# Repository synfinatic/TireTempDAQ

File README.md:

# TireTempDAQ

## About
This project is designed to add IR  temperature sensors to your existing data logger.  The initial design for this project will support up to 4 sensors and output 4 linear analog outputs (0 to 4.096V) to your data logger (GPX Pro, AiM, Race-Technology, AEM, MoTeC, GEMS, etc).

This project will include three main parts:

 * CadSoft Eagle files for the PCB designs
 * Arduino compatible software for the [PRJC Teensy-LC](http://www.prjc.com/teensy/teensyLC.html) micro-controller
 * [Autodesk Fusion 360](http://www.autodesk.com/products/fusion-360/overview) CAD designs of the cases for the sensor & controller modules which can then be manufactured via 3D printing ABS/PLA or CNC aluminum.
 
## Design
The key component will be the [Melexis MXL90614](http://www.melexis.com/Infrared-Thermometer-Sensors/Infrared-Thermometer-Sensors/Digital-plug--play-infrared-thermometer-in-a-TO-can-615.aspx) IR temperature sensor.  This sensor is a small yet accurate IR sensor able to measure the temperature of other objects without touching them- perfect for tires on a car or motorcycle!

Each sensor sends it's data via a thin single cable of 4 wires to the "brains" which decodes the digital signals from each sensor and then relays that to your data logger via a standard linear analog output.  This conversion process ensures that TireTempDAQ will be compatible with virtually any data aquision system you can imagine!

## License
All files are released under the [GPLv3](http://www.gnu.org/licenses/gpl-3.0.en.html).

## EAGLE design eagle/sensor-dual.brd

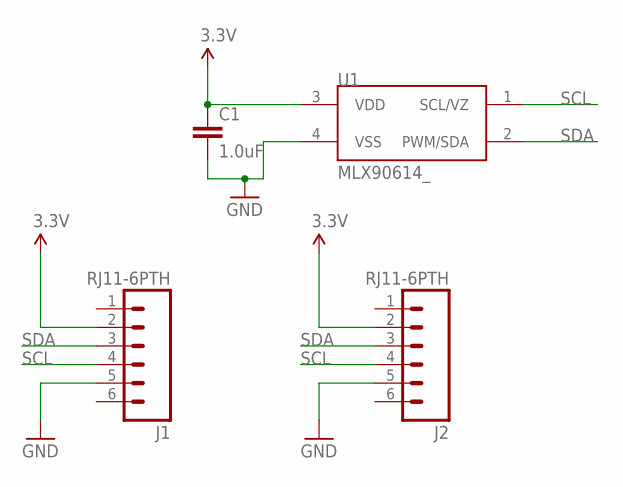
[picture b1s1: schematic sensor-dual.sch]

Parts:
C1: 1.0uF; 0805
J1, J2: RJ11-6PTH; RJ11-6
U1: MLX90614_; TO-39

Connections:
3.3V: C1.1, J1.2, J2.2, U1.3 (VDD)
GND: C1.2, J1.5, J2.5, U1.4 (VSS)
SCL: J1.4, J2.4, U1.1 (SCL/VZ)
SDA: J1.3, J2.3, U1.2 (PWM/SDA)

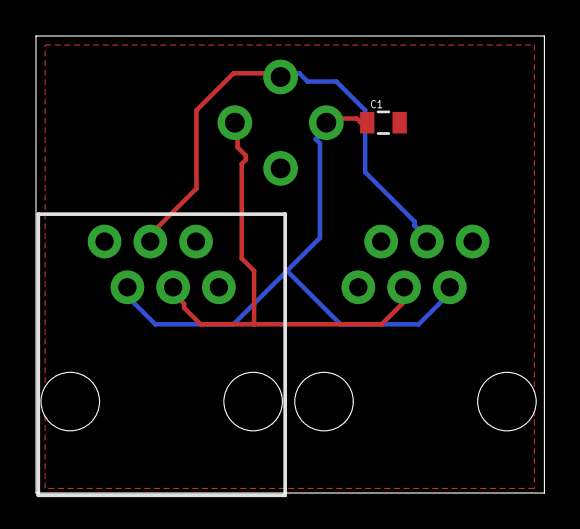
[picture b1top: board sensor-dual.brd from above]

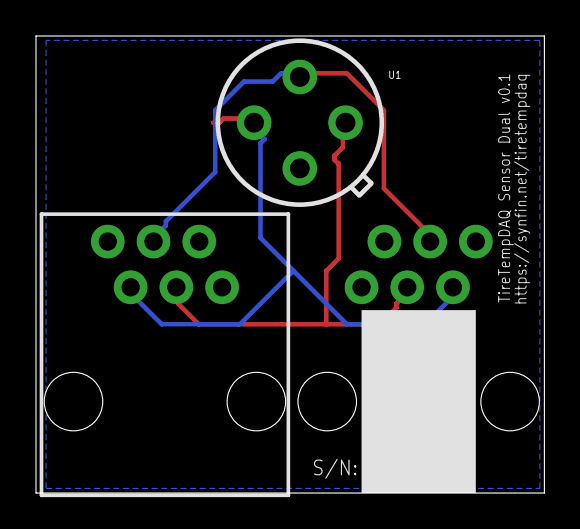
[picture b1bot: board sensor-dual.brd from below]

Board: 2 copper layers, 28.2 x 25.4 mm, 4 parts (2 on the bottom side), 4 nets.

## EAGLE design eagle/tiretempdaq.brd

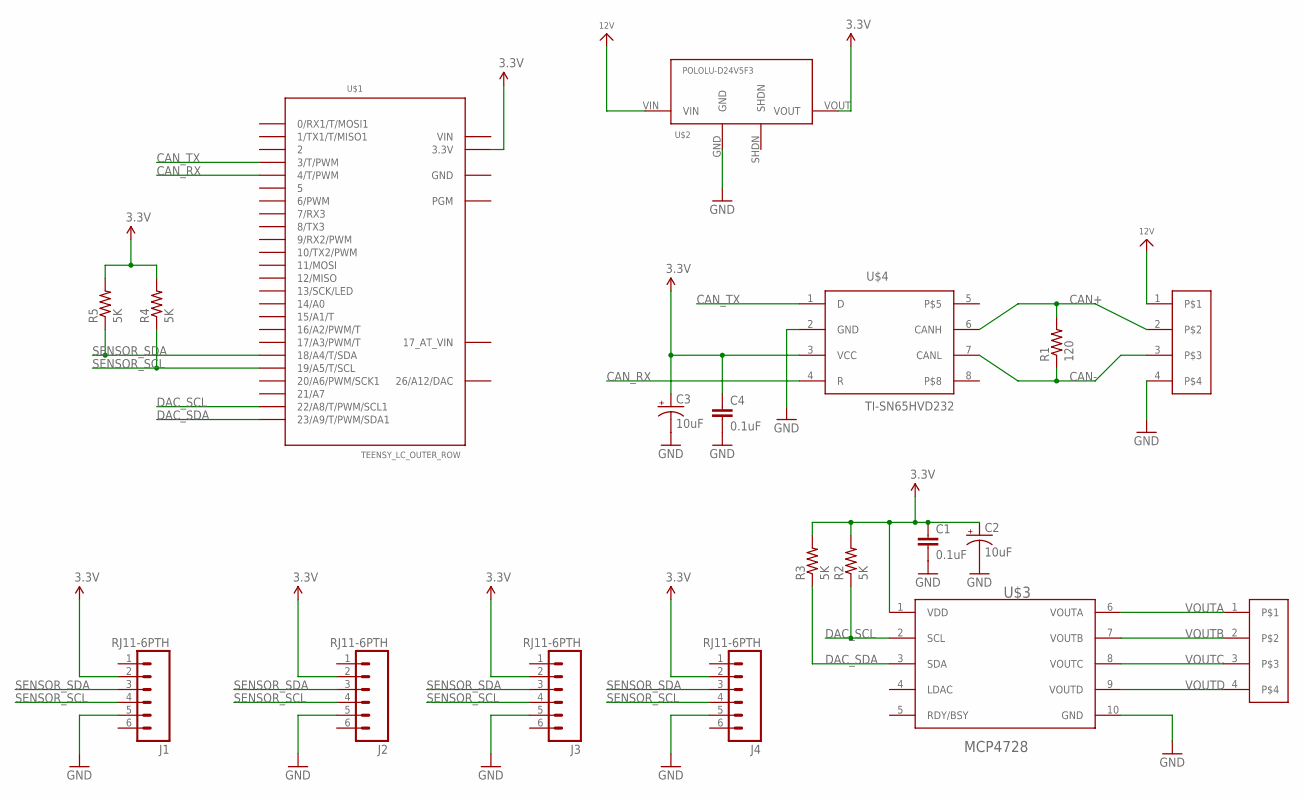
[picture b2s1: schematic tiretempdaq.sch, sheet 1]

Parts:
C1, C4: 0.1uF; 0603-CAP
C2, C3: 10uF; EIA3216
J1, J2, J3, J4: RJ11-6PTH; RJ11-6
J5, J6: TERM-BLOCK-P4-3.5OST-TE-3.5-4P; TERM-4P-3.5
R1: 120; 0805
R2, R3, R4, R5: 5K; 0805
U$1: TEENSY_LC_OUTER_ROW; TEENSY3-OUTER_ROW
U$2: POLOLU-D24V5F3; POLOLU-DC-4PIN
U$3: MCP4728; MSOP-10
U$4: TI-SN65HVD232; SOIC8

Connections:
3.3V: C1.1, C2.A (+), C3.A (+), C4.1, J1.2, J2.2, J3.2, J4.2, R2.2, R3.2, R4.2, R5.2, U$1.3.3V, U$1.3.3V1 (3.3V), U$2.VOUT, U$3.1 (VDD), U$4.3 (VCC)
12V: J5.1, U$2.VIN
26/A12/DAC: U$1.RESET/DAC (26/A12/DAC)
CAN+: J5.2, R1.2, U$4.6 (CANH)
CAN-: J5.3, R1.1, U$4.7 (CANL)
CAN_RX: U$1.4 (4/T/PWM), U$4.4 (R)
CAN_TX: U$1.3 (3/T/PWM), U$4.1 (D)
DAC_SCL: R2.1, U$1.22/A8 (22/A8/T/PWM/SCL1), U$3.2 (SCL)
DAC_SDA: R3.1, U$1.23/A9 (23/A9/T/PWM/SDA1), U$3.3 (SDA)
GND: C1.2, C2.C (-), C3.C (-), C4.2, J1.5, J2.5, J3.5, J4.5, J5.4, U$1.AGND (GND), U$1.GND, U$1.GND1 (GND), U$2.GND, U$3.10 (GND), U$4.2 (GND)
SENSOR_SCL: J1.4, J2.4, J3.4, J4.4, R4.1, U$1.19/A5 (19/A5/T/SCL)
SENSOR_SDA: J1.3, J2.3, J3.3, J4.3, R5.1, U$1.18/A4 (18/A4/T/SDA)
VIN: U$1.VIN
VOUTA: J6.1, U$3.6 (VOUTA)
VOUTB: J6.2, U$3.7 (VOUTB)
VOUTC: J6.3, U$3.8 (VOUTC)
VOUTD: J6.4, U$3.9 (VOUTD)

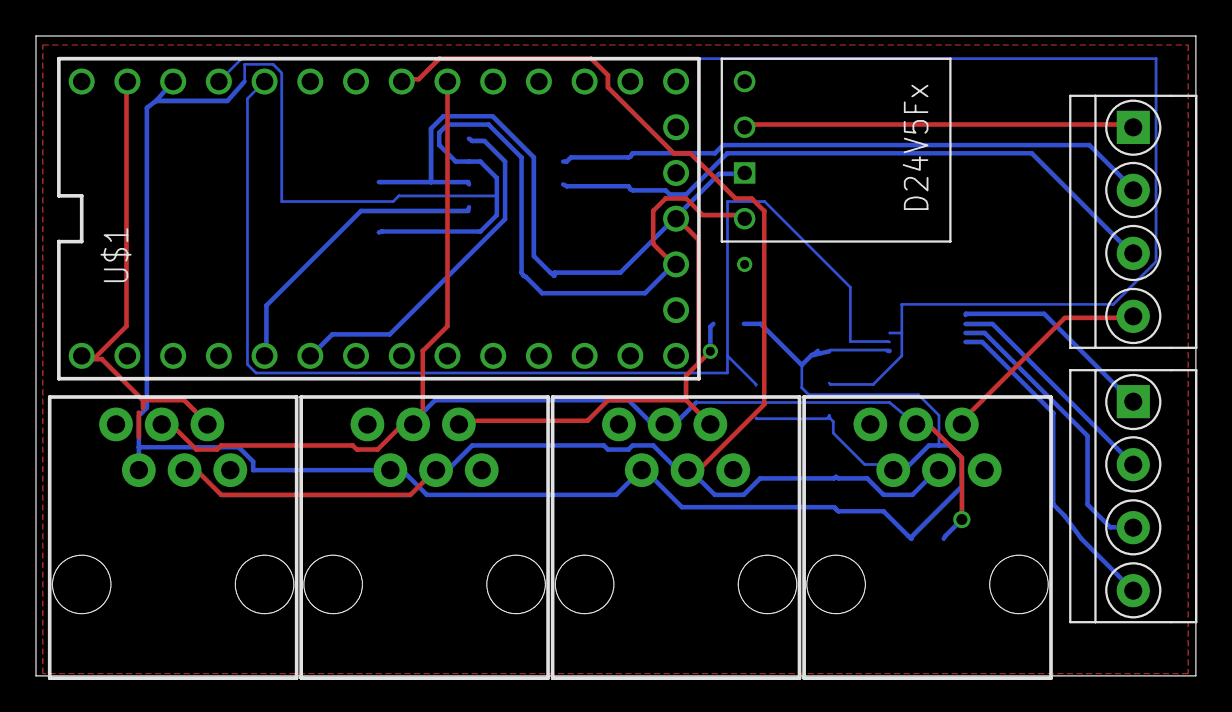
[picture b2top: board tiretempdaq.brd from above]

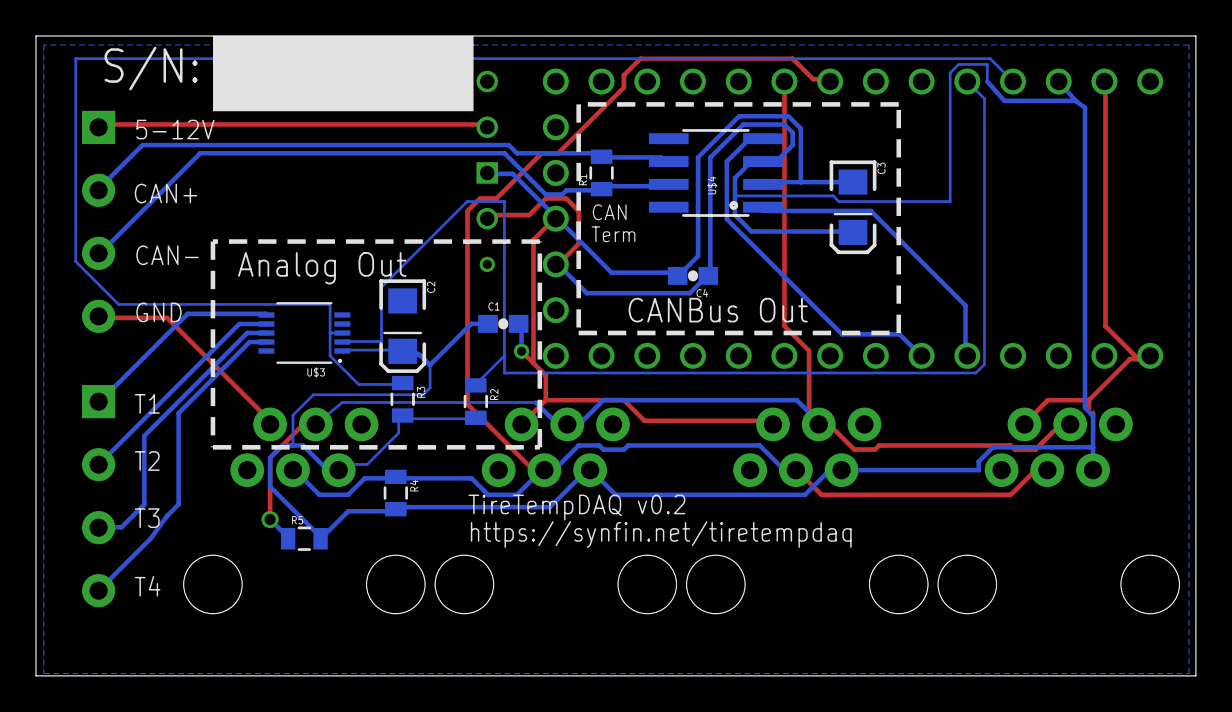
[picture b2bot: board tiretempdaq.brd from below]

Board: 2 copper layers, 64.4 x 35.5 mm, 19 parts (11 on the bottom side), 15 nets.

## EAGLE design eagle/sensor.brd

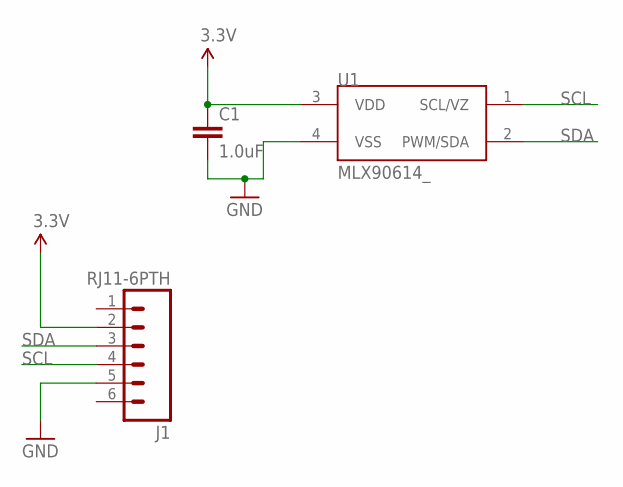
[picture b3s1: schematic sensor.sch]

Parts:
C1: 1.0uF; 0805
J1: RJ11-6PTH; RJ11-6
U1: MLX90614_; TO-39

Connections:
3.3V: C1.1, J1.2, U1.3 (VDD)
GND: C1.2, J1.5, U1.4 (VSS)
SCL: J1.4, U1.1 (SCL/VZ)
SDA: J1.3, U1.2 (PWM/SDA)

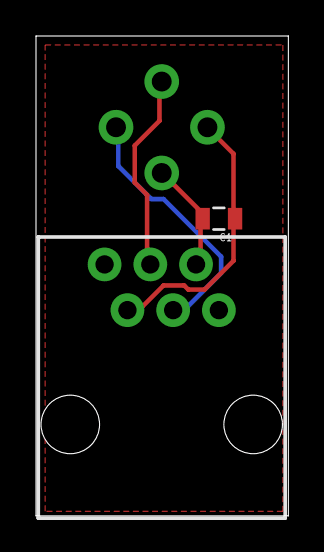
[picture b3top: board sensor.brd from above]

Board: 2 copper layers, 14.0 x 26.7 mm, 3 parts (1 on the bottom side), 4 nets.

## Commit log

2016-01-26 First pass at PCB v0.1
    - Support for both Analog & CANBus outputs
    - 4 RJ11 SMBus/I2C input connectors
    - Support for Teensy-LC for Analog output
    - Support for Teensy-3.1 & 3.2 for CANBus output
2016-01-27 Update board to v0.2 & create v0.1 sensor board
    - Re-layout main board to put all analog parts closer together
    - Sensor board v0.1
2016-05-12 Add sensor-dual board
    This board has one sensor, but an In & Out jack for daisy chaining
    sensors to reduce the amount of wires you need to run back to the
    main unit.

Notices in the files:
parts and their libraries:
SparkFun-Capacitors: Licensing: Creative Commons ShareAlike 4.0 International - https://creativecommons.org/licenses/by-sa/4.0
microbuilder: This work is placed in the public domain, and may be freely used for commercial and non-commercial work with the following conditions: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
